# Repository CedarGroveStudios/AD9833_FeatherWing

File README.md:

### _A precision waveform generator FeatherWing_
# AD9833_FeatherWing

## Overview
The AD9833 Precision Waveform Generator FeatherWing is an Adafruit Feather-compatible module. The Waveform Generator produces an op-amp buffered sine, triangle, or square wave output with a practical frequency range of 0.5Hz to 100KHz with 0.1Hz resolution.  
  * Frequency accuracy and stability is determined by the on-board 25MHz +/- 100ppm crystal oscillator (Abracon ASV-25.000MHZ-E-T).  
  * Waveform Generator control is via the Feather SPI bus; chip select is provided by the D6 GPIO pin.  
  *	Output signal peak-to-peak amplitude is adjustable with a maximum unipolar output of slightly less than 3.3 volts.  
  *	Output can optionally be connected to the A2 analog input pin via an on-board jumper for real-time output signal monitoring.  
  *	The wing derives its power from the host Feather's 3.3V power.  

The AD9833 Precision Waveform Generator FeatherWing was tested with a Feather M4 Express using CircuitPython version 4.1.0 rc-1. Example sweep generator code is provided in the repository (sweep example video: https://youtu.be/O1vMfLoCWzg). 

OSH Park project: https://oshpark.com/shared_projects/al6aPN0u

Refer to the Analog Devices' AD9833 Waveform Generator data sheet for device control protocol details.

## Primary Project Objectives
1)	Generate useful waveforms in the audio frequency range
  a.	Highly accurate and stable absolute frequency: ±0.5Hz, 1000ppm  
  b.	Moderately accurate waveform shape: 8-bit minimum  
  c.	Fixed 3.0 volt peak-to-peak output, centered at 1.5 volts  
2)	Implement with CircuitPython code
3)	Increase SPI communications knowledge
4)	Improve SMD soldering skills
5)	Improve conceptual knowledge  
  a.	SPI communications  
  b.	Swept frequency control  
  c.	Digital signal generation  
  d.	CircuitPython device drivers  
  e.	ADSR envelope modulation (optional)  
6)	Fabricate physical equipment  
  a.	Workbench fixed and swept signal generator  
  b.	MIDI and CV controlled LFO and audio frequency Eurorack oscillator module  

## Deliverables
1)	Custom FeatherWing PCB, M4 Express pinout
2)	FeatherWing Implementation Chart
3)	CircuitPython device driver
4)	CircuitPython examples and test code
5)	KiCAD schematic and board layout with Gerber code
6)	OSH Park public shared project page
7)	GitHub public repository page
8)	Project description and report
9)	Workbench signal generator
10)	Eurorack module
## Concepts Learned
1)	Solder paste stencil was essential for successful SOT-23 and MSOP-10 component soldering
2)	10-bit waveform accuracy will be sufficient for most anticipated uses
3)	Waveform output amplitude was very stable from 0 to 250kHz
4)	Output buffer op-amp gain-bandwidth product limit contributes significantly to high frequency roll-off but also smooths the digital feedthrough components of the waveform
5)	The low peak of the waveform only reaches +150mV not 0V as anticipated
6)	Waveform generator DAC output filtering capacitance was listed incorrectly in the datasheet example; value used for manufacturer testing was correct
7)	Separate analog ground on the PCB helped to reduce analog output digital noise
8)	ADSR envelope generation will require additional circuitry (see https://github.com/CedarGroveStudios/AD9833_ADSR_FeatherWing for the full discussion of tests)
9)	Output frequency change throughput of the CircuitPython example code (using the cedargrove_AD9833 library) is approximately 450usec, allowing for frequency sweep steps and modulation rates of > 2k changes(steps) per sec
10)	CircuitPython driver code was simpler to create than anticipated  
  a.	CircuitPython SPI communications techniques are well-documented  
  b.	Command register protocol was thoroughly explained in the device datasheet  
  c.	Non-typical clock polarity was the only issue to overcome  
## Next Steps
  * Finish the ADSR envelope generation tests and incorporate additional components in the v02 PCB design
  *	Replace the existing op-amp with higher gain-bandwidth version
  *	Consider a FeatherWing-sized dual-output version
  *	Incorporate the knowledge and experience gained in this project with the design of an Arbitrary Waveform Generator FeatherWing

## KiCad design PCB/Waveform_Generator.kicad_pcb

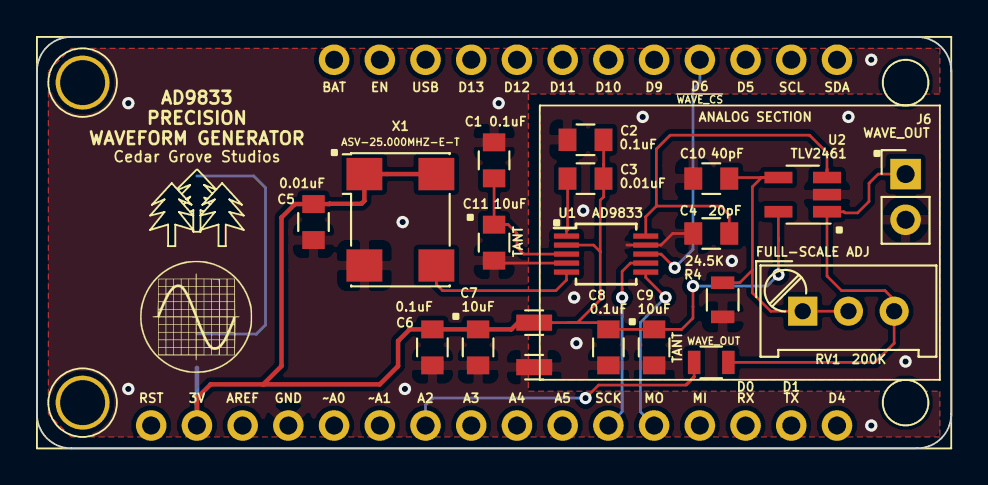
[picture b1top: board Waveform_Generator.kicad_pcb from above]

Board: 2 copper layers, 50.8 x 22.9 mm, 23 parts (1 on the bottom side), 15 nets.

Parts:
C1, C2, C6, C8: 0.1uF; C_0805
C3, C5: 0.01uF; C_0805
C4: 20pF; C_0805
C7, C9, C11: 10uF; C_0805
C10: 40pF; C_0805
D1: GRN; Cedar_Grove_logo_lighted
J6: WAVE_OUT; Pin_Header_Straight_1x02_Pitch2.54mm
M1: Feather_M4_Express; Adafruit_Feather_M4_Express_bare
R1: 470; R_0805
R2, R3: 0; NetTie_0603
R4: 24.5K; R_0805
R5: 0; R_0805
RV1: 200K; Potentiometer_Trimmer_Bourns_PV36W
U1: AD9833; MSOP-10_3x3mm_Pitch0.5mm
U2: TLV2461; SOT-23-5_HandSoldering
X1: ASV-25.000MHZ-E-T; Oscillator_SMD_Abracon_ASV-4pin_7.0x5.1mm

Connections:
+3.3VA: C2.1, C3.1, C8.1, C9.1, R2.1, U1.2, U2.5
+3V3: C5.1, C6.1, C7.1, M1.2, R1.2, R2.2, X1.1, X1.4
/25MHZ_CLK: U1.5, X1.3
/MOSI: M1.12, U1.6
/SCLK: M1.11, U1.7
/WAVE_OUT: M1.7, R5.1
/~WAVE_CS: M1.25, U1.8
GND: C1.2, C5.2, C6.2, C7.2, C11.2, D1.1, M1.4, R3.2, U1.4, X1.2
GNDA: C2.2, C4.2, C8.2, C9.2, C10.2, J6.2, R3.1, R4.1, U1.9, U2.2
unnamed: C1.1, C11.1, U1.3
unnamed: C3.2, U1.1
unnamed: C4.1, U1.10, U2.3
unnamed: C10.1, R4.2, RV1.1, RV1.2, U2.4
unnamed: D1.2, R1.1
unnamed: J6.1, R5.2, RV1.3, U2.1

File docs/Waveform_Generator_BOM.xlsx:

Reference | Value | Desc | Footprint | DigiKey
C1 | 0.1uF | capacitor | 0805
C10 | 40pF | capacitor | 0805
C11 | 10uF | capacitor | 0805
C2 | 0.1uF | capacitor | 0805
C3 | 0.01uF | capacitor | 0805
C4 | 20pF | capacitor | 0805
C5 | 0.01uF | capacitor | 0805
C6 | 0.1uF | capacitor | 0805
C7 | 10uF | capacitor | 0805
C8 | 0.1uF | capacitor | 0805
C9 | 10uF | capacitor | 0805
D1 | GRN | LED | 0805
J6 | WAVE_OUT | 2-pin header | 1x02_Pitch2.54mm
R1 | 470 ohm | resistor | 0805
R4 | 24.5K | resistor | 0805
RV1 | 200K | potentiometer | Trimmer_Bourns_PV36W
U1 | AD9833 | waveform generator | MSOP-10_3x3mm_Pitch0.5mm
U2 | TLV2461 | op-amp | SOT-23-5
X1 | ASV-25.000MHZ-E-T | oscillator | ASV-4pin_7.0x5.1mm

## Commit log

2019-07-22 inital repo load
2019-07-22 initial version
2019-07-22 Initial release
2019-07-23 code example updated to smooth sweep transitions
2019-07-24 add transport helpers
2019-07-24 not ready for prime time
2019-07-24 add library UI concept drawing
2019-07-24 fix wave_type issues
2019-07-24 fixed wave_type issue
2019-07-28 initial library deployment
2019-07-29 eliminate potential for startup noise
2019-07-29 updated driver class and file naming to align better with Adafruit's
2019-08-01 updated ADSR example to include note velocity and envelop smoothing
2019-08-01 add velocity and portamento
2019-08-06 update featherwing impl chart
2019-08-06 include impl chart
2019-08-06 updated documentation and BOM
2019-08-06 update BOM spreadsheet
2019-08-06 add wing impl chart
2019-08-06 update impl chart
2019-08-21 custom schematic symbol for AD9833
2019-08-21 added custom schematic symbol for AD9833
2019-09-03 update photos
2019-11-02 update BOM and Impl Chart
2021-07-12 update documentation
2022-09-02 update license
2022-10-12 move code to AD9833_ADSR
2022-10-12 initial repo load
